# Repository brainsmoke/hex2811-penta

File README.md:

Hex2811 Penta
=============

A 16x WS2812/SK6812 ledstrip driver for my [LED ball with 900 SK6812 LEDs](https://www.youtube.com/watch?v=lAXNFTupz5I).

Essentially a clone to the awesome [fadecandy](https://github.com/scanlime/fadecandy) board,
but with a faster MCU and a second buffer chip connected to PORTC bits 0-7, allowing me to
drive [16x80 RGB chips](https://github.com/brainsmoke/HexWS2811), or 16x60 RGBW chips.

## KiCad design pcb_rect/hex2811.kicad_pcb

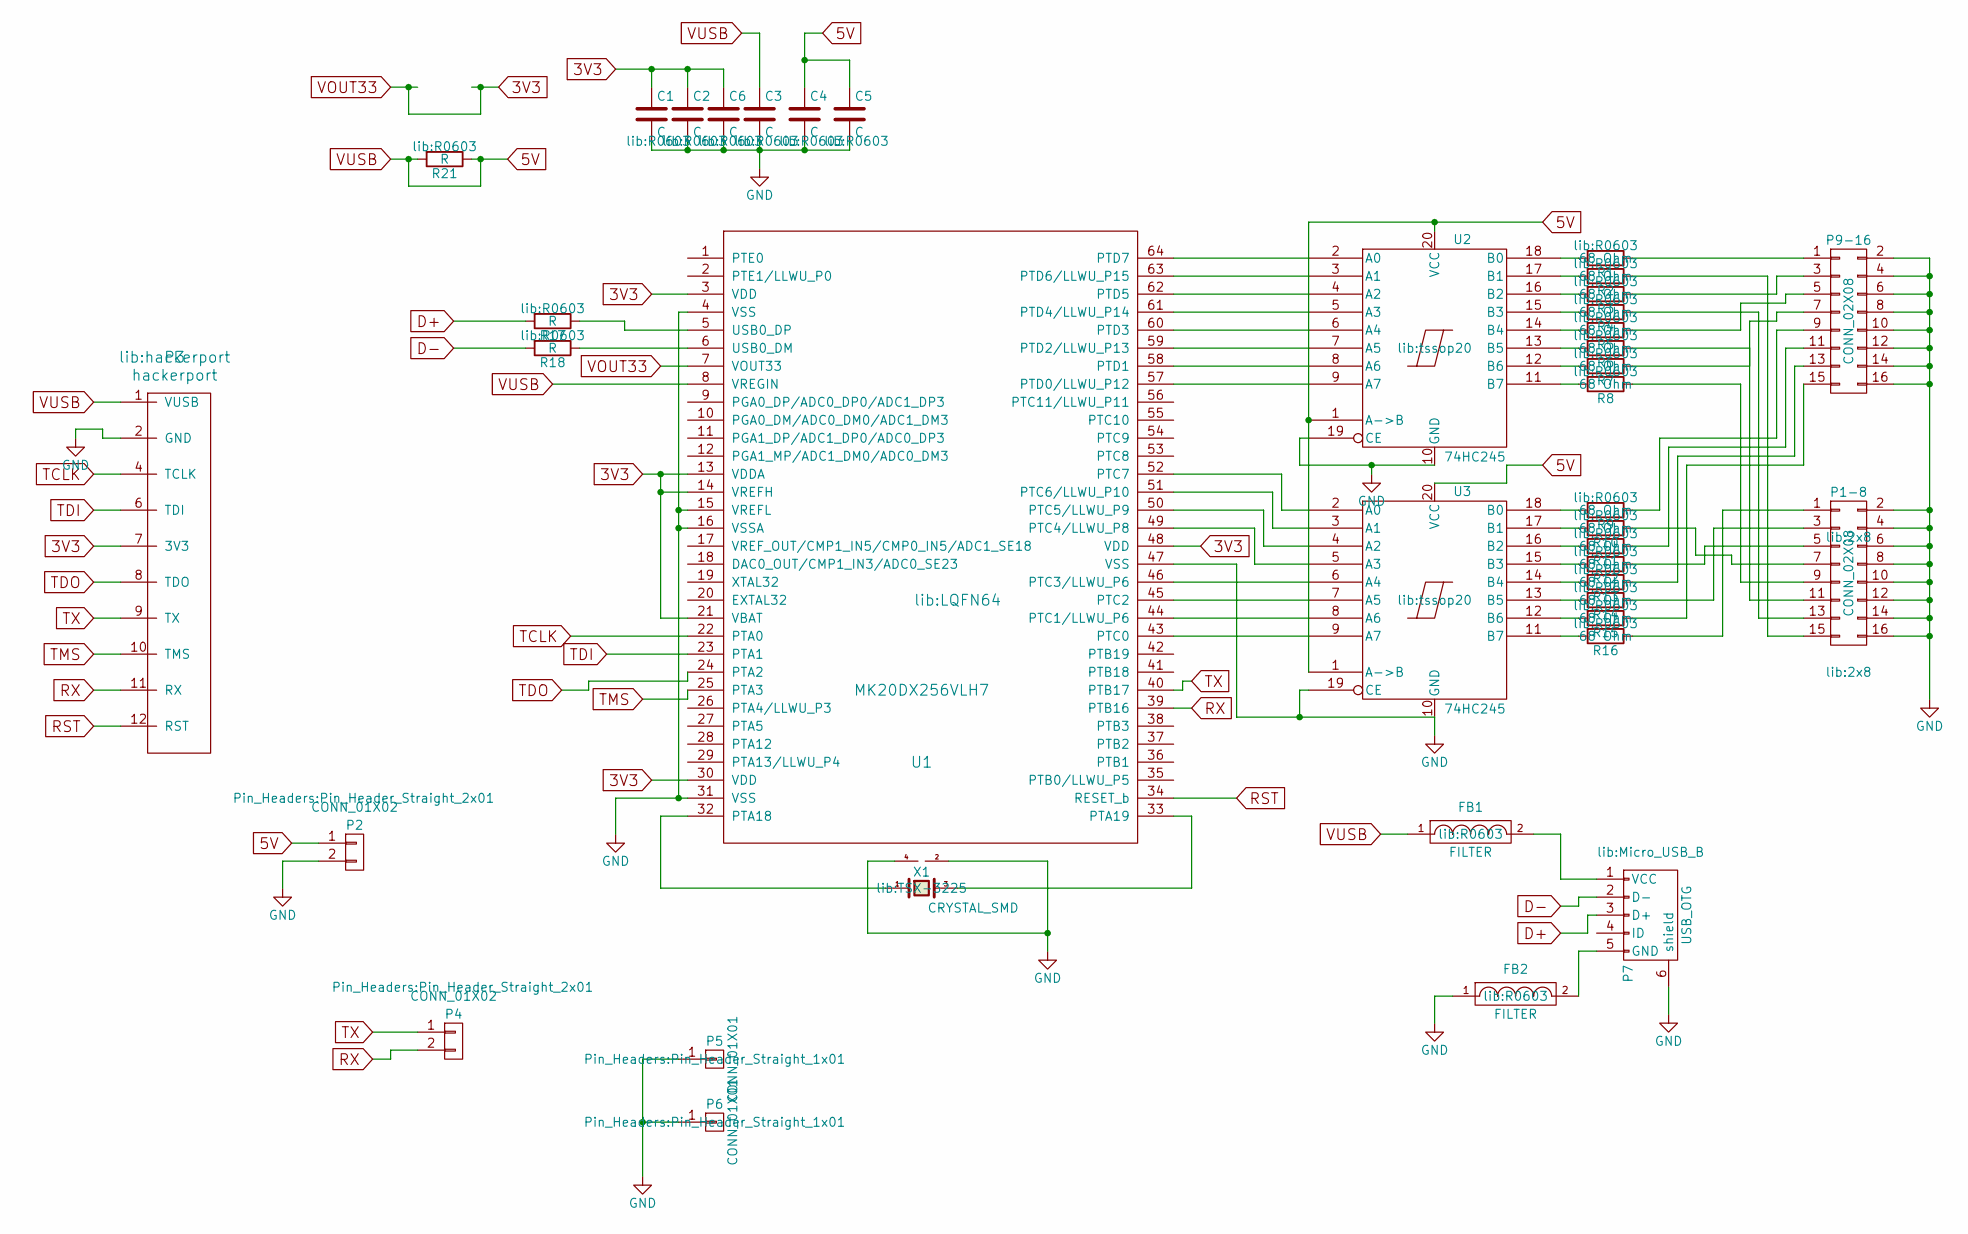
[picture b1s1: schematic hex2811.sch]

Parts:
C1, C2, C3, C4, C5, C6: C; R0603
FB1, FB2: FILTER; R0603
P1-8, P9-16: CONN_02X08; 2x8
P2, P4: CONN_01X02; Pin_Header_Straight_2x01
P3: hackerport
P5, P6: CONN_01X01; Pin_Header_Straight_1x01
P7: USB_OTG; Micro_USB_B
R1, R2, R3, R4, R5, R6, R7, R8, R9, R10, R11, R12, R13, R14, R15, R16: 68 Ohm; R0603
R17, R18, R21: R; R0603
U1: MK20DX256VLH7; LQFN64
U2, U3: 74HC245; tssop20
X1: CRYSTAL_SMD; TSX-3225

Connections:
3V3: C1.1, C2.1, C6.1, P3.7 (3V3), U1.3 (VDD), U1.7 (VOUT33), U1.13 (VDDA), U1.14 (VREFH), U1.21 (VBAT), U1.30 (VDD), U1.48 (VDD)
5V: C3.1, C4.1, C5.1, FB1.1, P2.1, P3.1 (VUSB), R21.1, R21.2, U1.8 (VREGIN), U2.1 (A->B), U2.20 (VCC), U3.1 (A->B), U3.20 (VCC)
D+: P7.3 (D+), R17.2
D-: P7.2 (D-), R18.2
GND: C1.2, C2.2, C3.2, C4.2, C5.2, C6.2, FB2.1, P1-8.2, P1-8.4, P1-8.6, P1-8.8, P1-8.10, P1-8.12, P1-8.14, P1-8.16, P2.2, P3.2 (GND), P5.1, P6.1, P7.6 (shield), P9-16.2, P9-16.4, P9-16.6, P9-16.8, P9-16.10, P9-16.12, P9-16.14, P9-16.16, U1.4 (VSS), U1.15 (VREFL), U1.16 (VSSA), U1.31 (VSS), U1.47 (VSS), U2.10 (GND), U2.19 (CE), U3.10 (GND), U3.19 (CE), X1.2 (GND), X1.4 (GND)
unnamed: FB1.2, P7.1 (VCC)
unnamed: FB2.2, P7.5 (GND)
unnamed: P1-8.1, R16.1
unnamed: P1-8.3, R14.1
unnamed: P1-8.5, R12.1
unnamed: P1-8.7, R10.1
unnamed: P1-8.9, R8.1
unnamed: P1-8.11, R6.1
unnamed: P1-8.13, R4.1
unnamed: P1-8.15, R2.1
unnamed: P9-16.1, R1.1
unnamed: P9-16.3, R3.1
unnamed: P9-16.5, R5.1
unnamed: P9-16.7, R7.1
unnamed: P9-16.9, R9.1
unnamed: P9-16.11, R11.1
unnamed: P9-16.13, R13.1
unnamed: P9-16.15, R15.1
unnamed: R1.2, U2.18 (B0)
unnamed: R2.2, U2.17 (B1)
unnamed: R3.2, U2.16 (B2)
unnamed: R4.2, U2.15 (B3)
unnamed: R5.2, U2.14 (B4)
unnamed: R6.2, U2.13 (B5)
unnamed: R7.2, U2.12 (B6)
unnamed: R8.2, U2.11 (B7)
unnamed: R9.2, U3.18 (B0)
unnamed: R10.2, U3.17 (B1)
unnamed: R11.2, U3.16 (B2)
unnamed: R12.2, U3.15 (B3)
unnamed: R13.2, U3.14 (B4)
unnamed: R14.2, U3.13 (B5)
unnamed: R15.2, U3.12 (B6)
unnamed: R16.2, U3.11 (B7)
unnamed: R17.1, U1.5 (USB0_DP)
unnamed: R18.1, U1.6 (USB0_DM)
unnamed: U1.32 (PTA18), X1.1
unnamed: U1.33 (PTA19), X1.3 (2)
unnamed: U1.43 (PTC0), U3.9 (A7)
unnamed: U1.44 (PTC1/LLWU_P6), U3.8 (A6)
unnamed: U1.45 (PTC2), U3.7 (A5)
unnamed: U1.46 (PTC3/LLWU_P6), U3.6 (A4)
unnamed: U1.49 (PTC4/LLWU_P8), U3.5 (A3)
unnamed: U1.50 (PTC5/LLWU_P9), U3.4 (A2)
unnamed: U1.51 (PTC6/LLWU_P10), U3.3 (A1)
unnamed: U1.52 (PTC7), U3.2 (A0)
unnamed: U1.57 (PTD0/LLWU_P12), U2.9 (A7)
unnamed: U1.58 (PTD1), U2.8 (A6)
unnamed: U1.59 (PTD2/LLWU_P13), U2.7 (A5)
unnamed: U1.60 (PTD3), U2.6 (A4)
unnamed: U1.61 (PTD4/LLWU_P14), U2.5 (A3)
unnamed: U1.62 (PTD5), U2.4 (A2)
unnamed: U1.63 (PTD6/LLWU_P15), U2.3 (A1)
unnamed: U1.64 (PTD7), U2.2 (A0)
RST: P3.12 (RST), U1.34 (RESET_b)
RX: P3.11 (RX), P4.2, U1.39 (PTB16)
TCLK: P3.4 (TCLK), U1.22 (PTA0)
TDI: P3.6 (TDI), U1.23 (PTA1)
TDO: P3.8 (TDO), U1.24 (PTA2)
TMS: P3.10 (TMS), U1.25 (PTA3)
TX: P3.9 (TX), P4.1, U1.40 (PTB17)

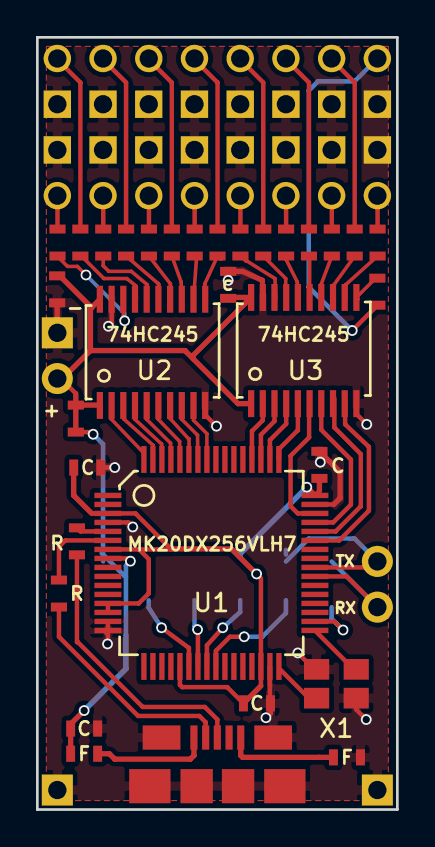
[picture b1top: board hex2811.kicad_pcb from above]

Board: 2 copper layers, 20.0 x 42.9 mm, 39 parts (1 on the bottom side), 66 nets.

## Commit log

2016-09-02 hexws pcb
2016-09-02 connect vbat
2016-10-07 move KiCAD files to pcb dir
2016-10-07 add firmware
2016-10-10 add drivers, readme
2016-10-10 make script look less hacky
2016-10-10 remove x
2017-08-28 add rectangular mini pcb
2017-08-28 commit cleaned-up firmware version
2017-09-07 drive up to 16 serial ports in parallel
2017-09-07 update comment
2017-09-07 remove debug statements
2020-12-10 Add edge ball (v1) and polyhedrone 2&3 drivers
